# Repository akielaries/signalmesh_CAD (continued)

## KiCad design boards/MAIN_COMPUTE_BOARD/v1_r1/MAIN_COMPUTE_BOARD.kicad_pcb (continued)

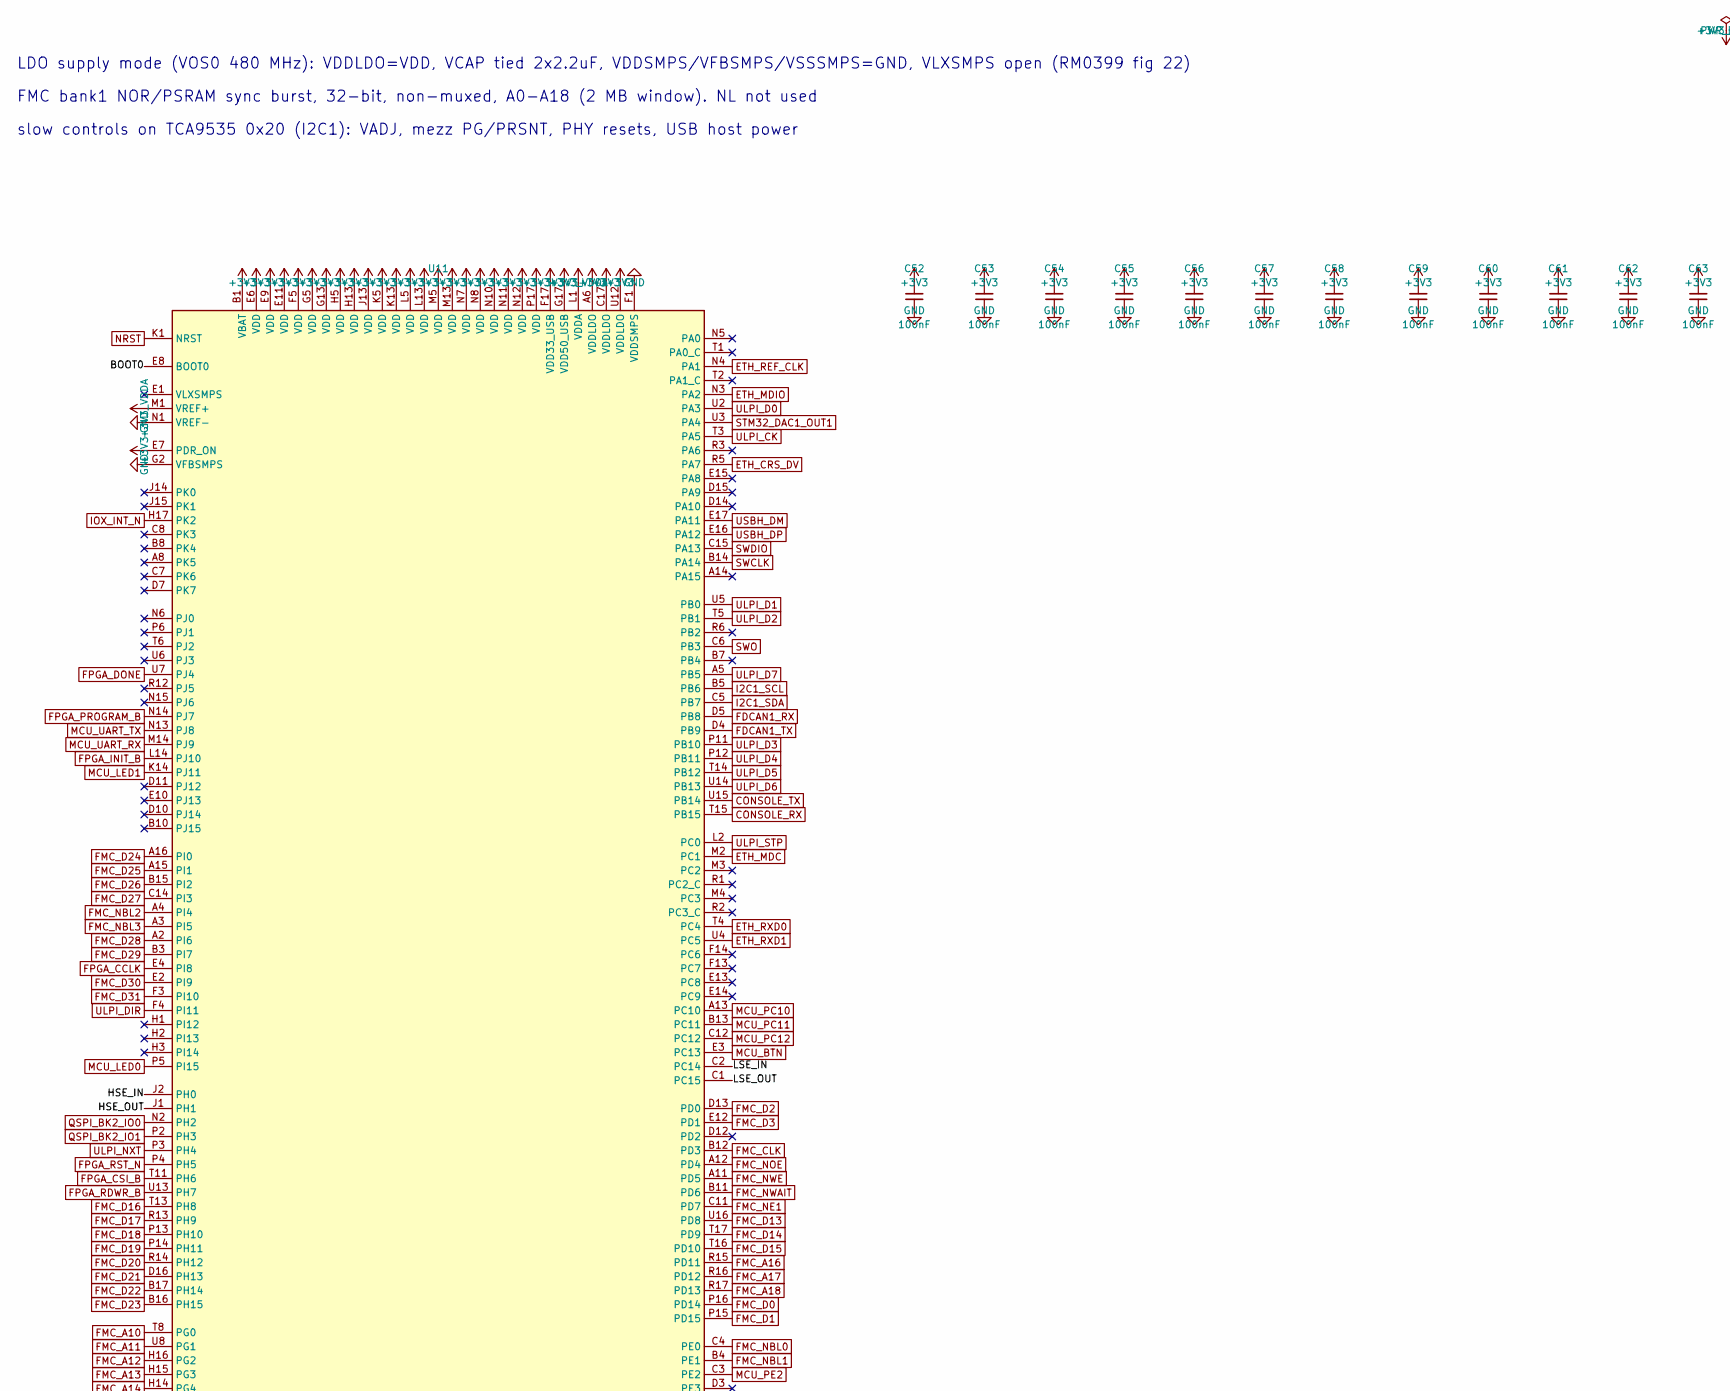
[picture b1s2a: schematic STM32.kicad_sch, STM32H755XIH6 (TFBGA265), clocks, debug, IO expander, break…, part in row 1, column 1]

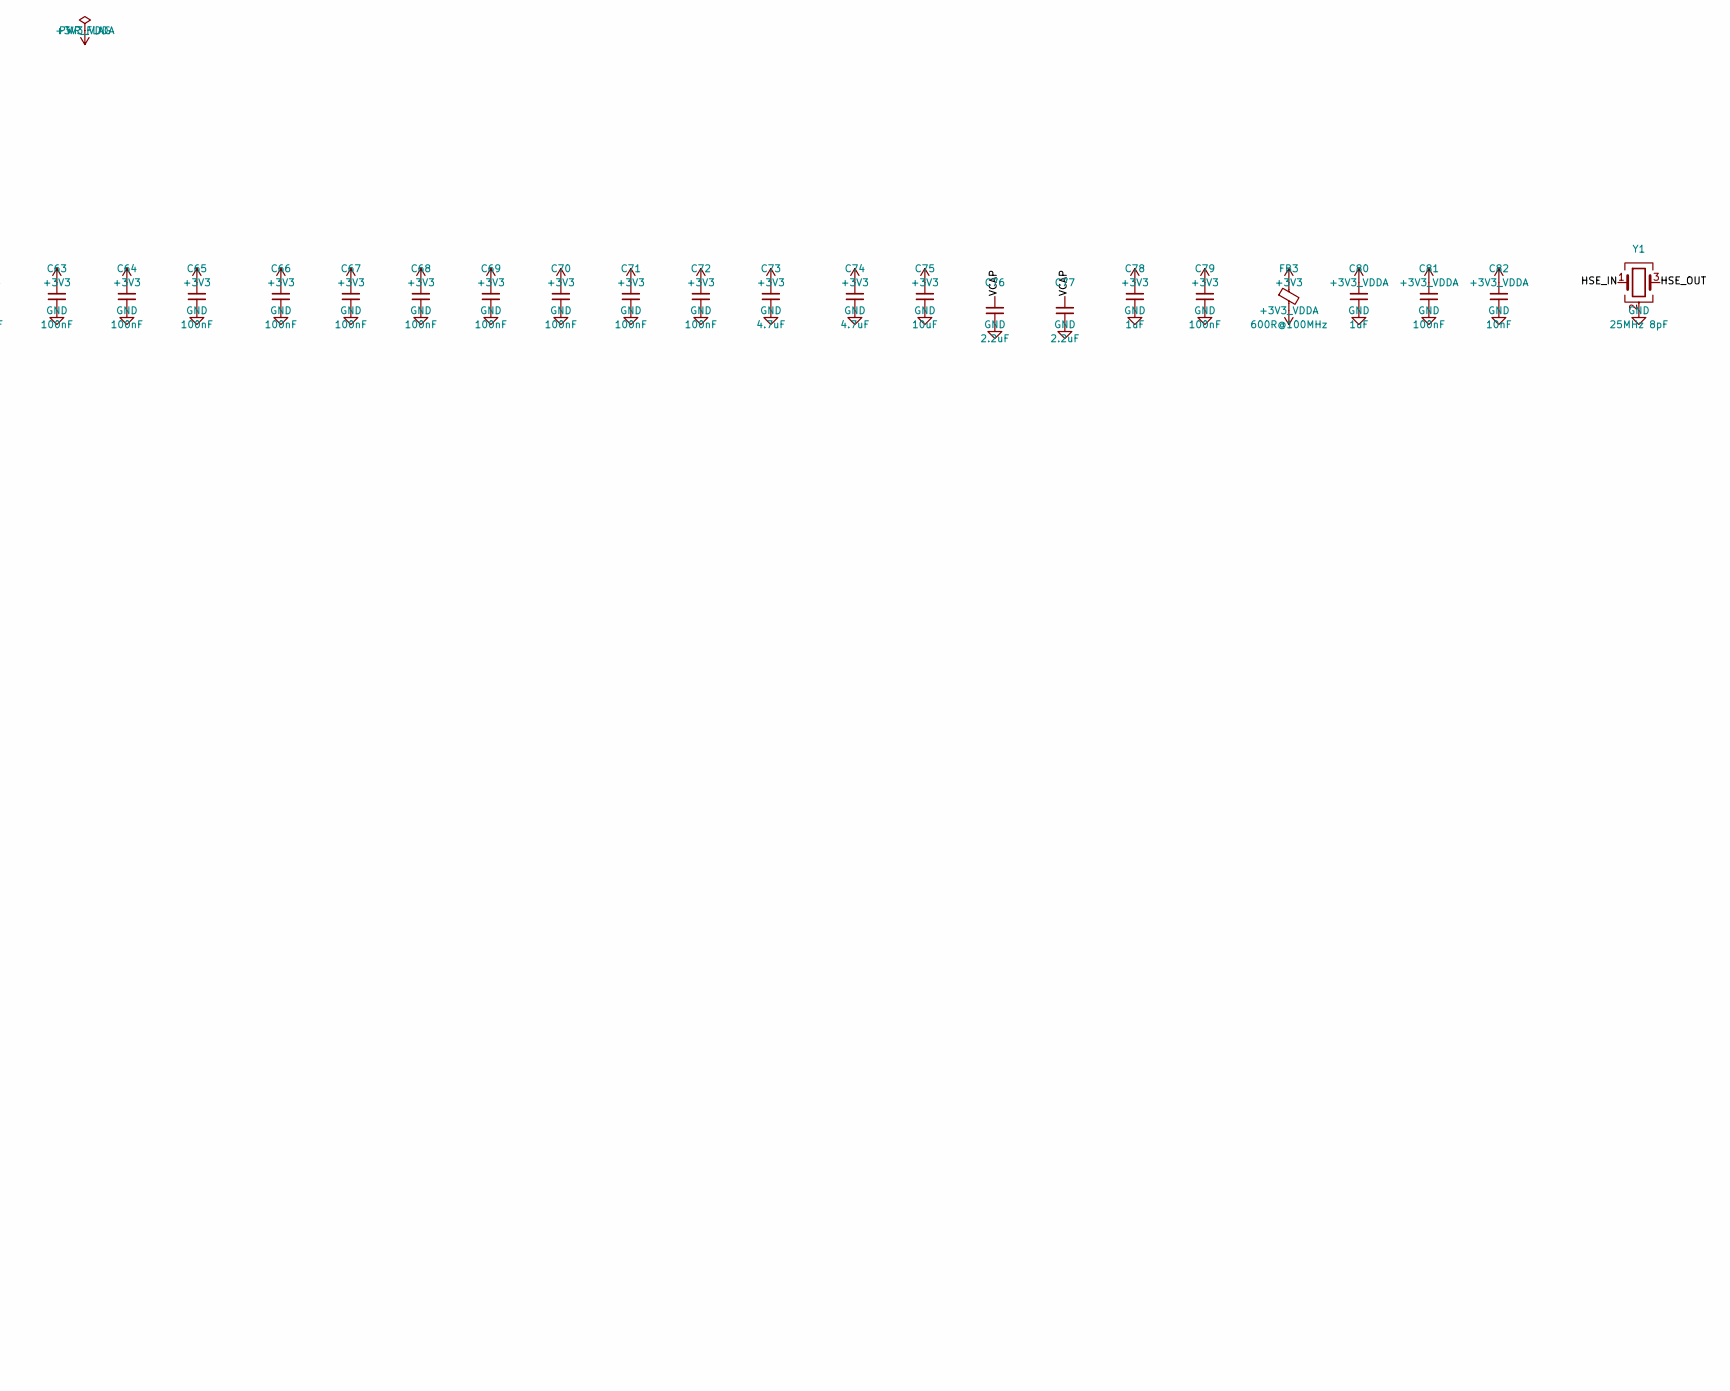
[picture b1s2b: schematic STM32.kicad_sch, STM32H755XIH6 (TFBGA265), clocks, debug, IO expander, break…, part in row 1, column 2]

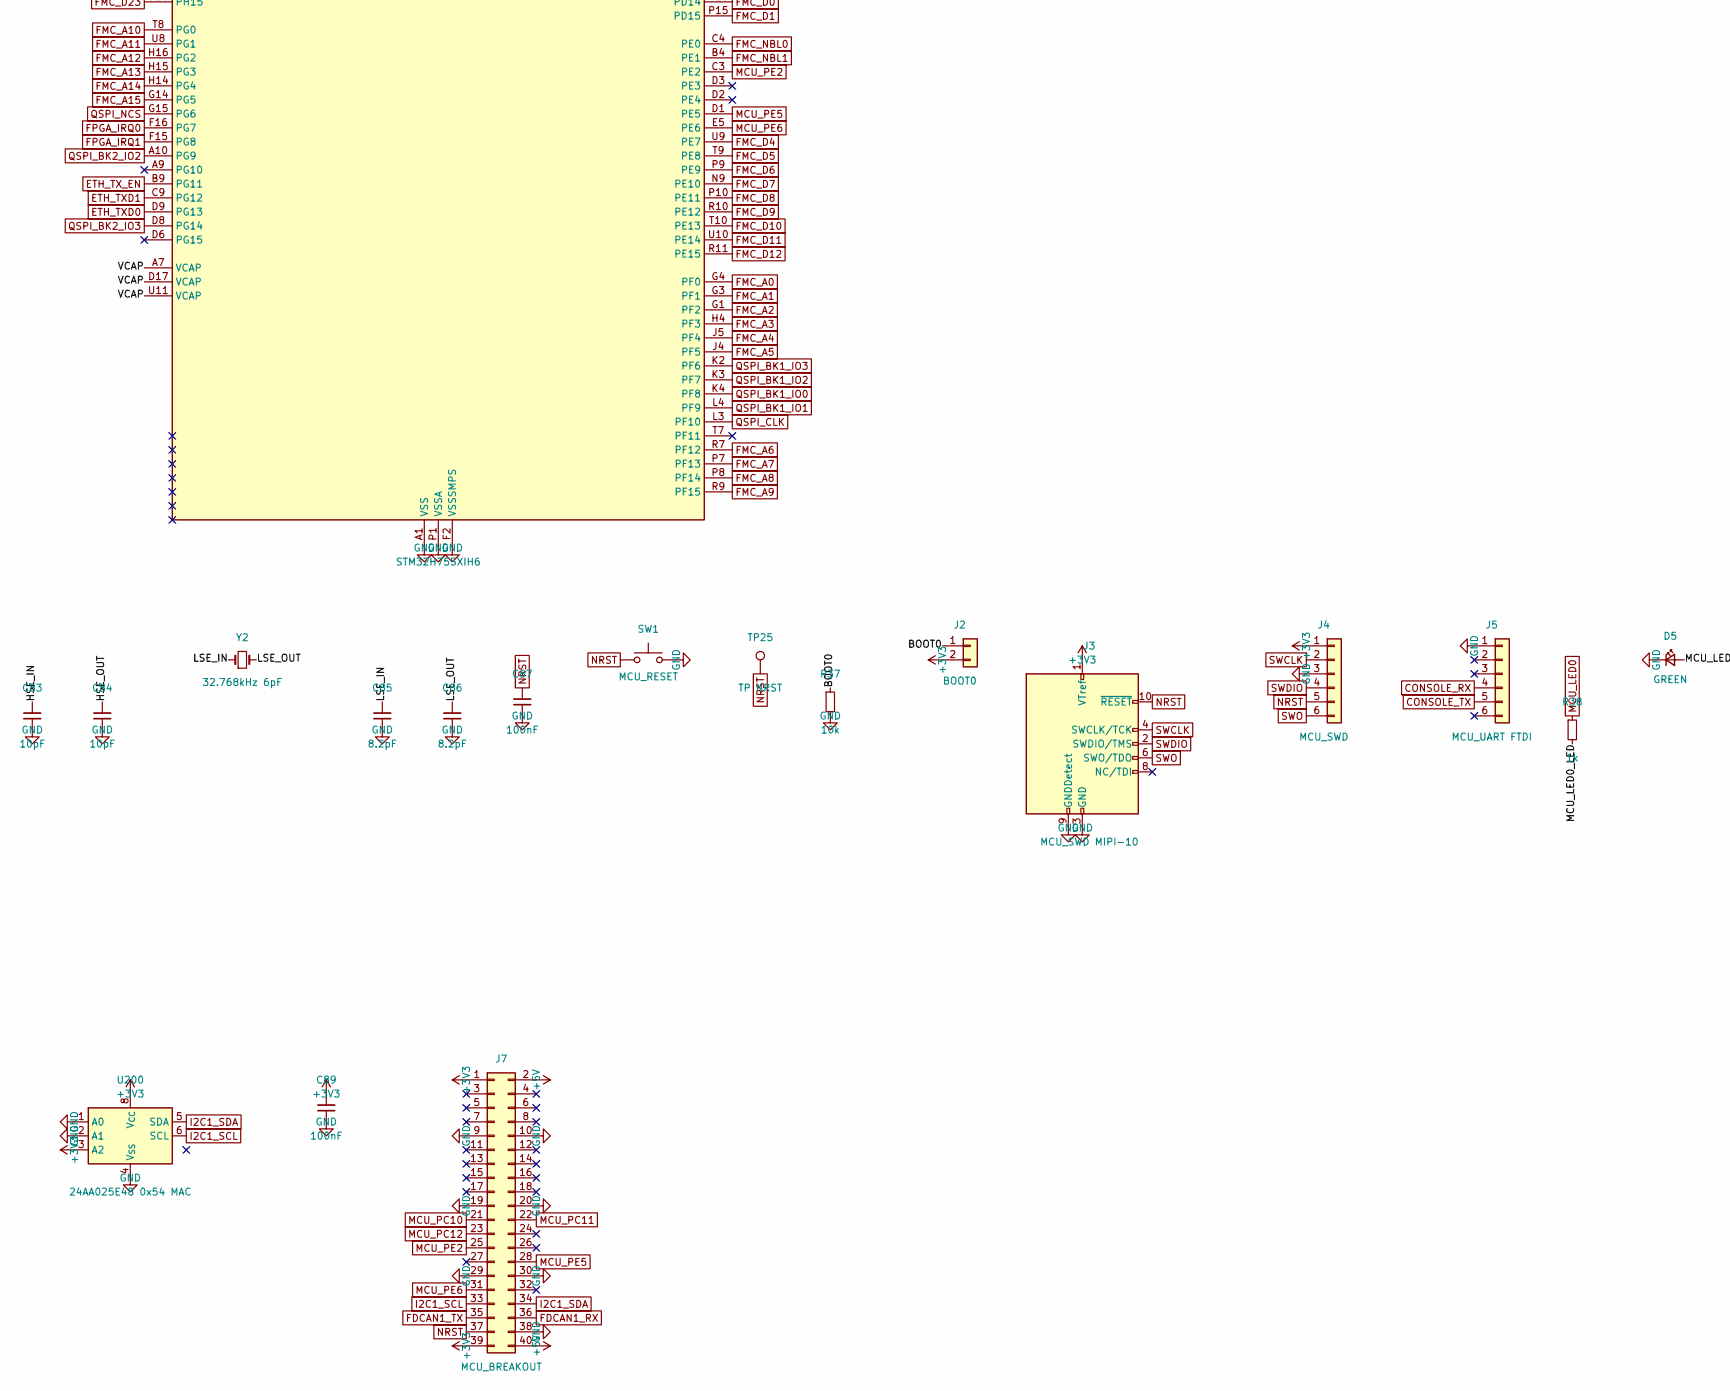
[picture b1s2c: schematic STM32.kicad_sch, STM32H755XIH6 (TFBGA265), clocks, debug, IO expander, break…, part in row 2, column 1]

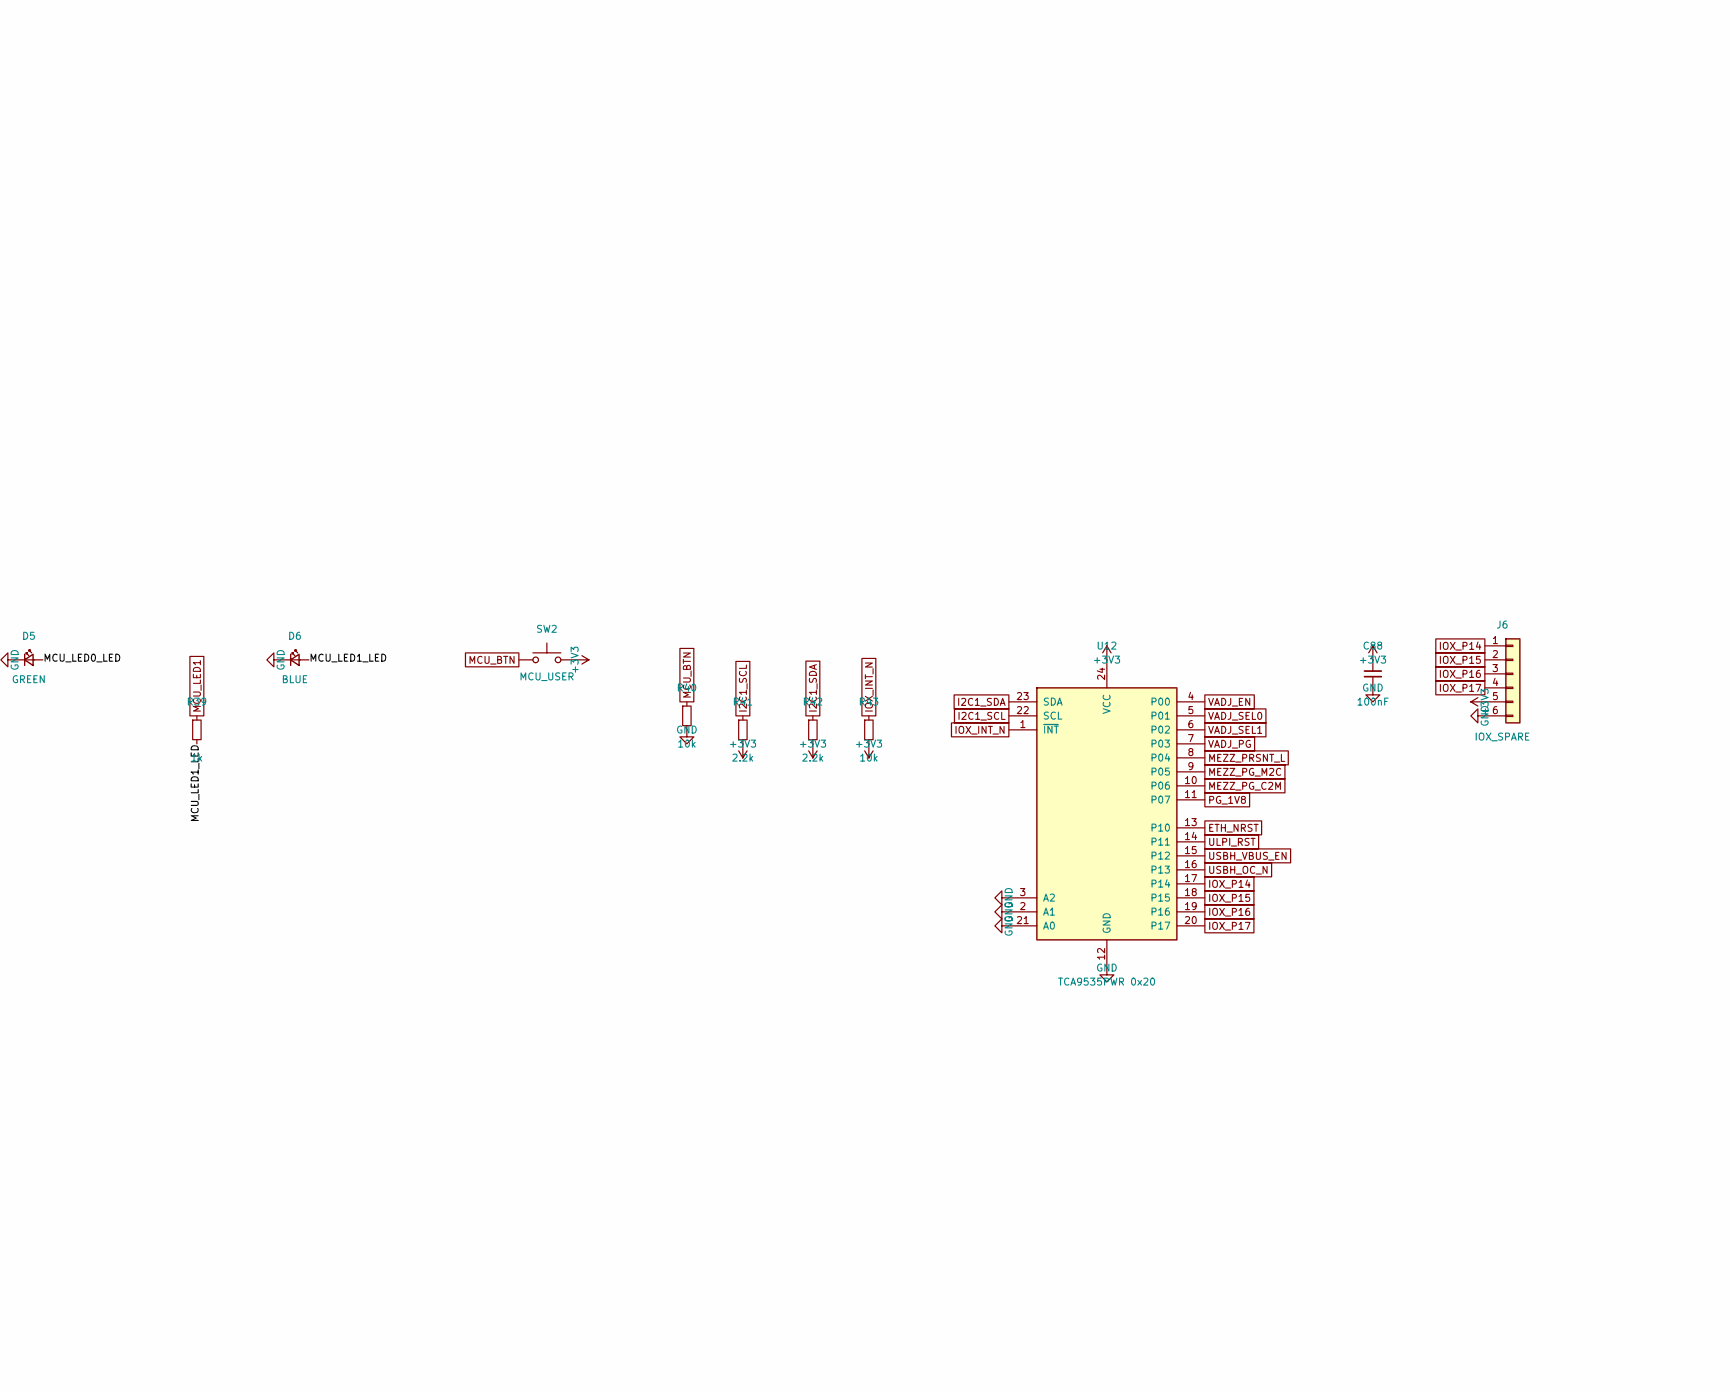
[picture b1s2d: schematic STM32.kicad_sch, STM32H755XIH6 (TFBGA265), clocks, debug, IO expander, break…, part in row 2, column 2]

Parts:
C52, C53, C54, C55, C56, C57, C58, C59, C60, C61, C62, C63, C64, C65, C66, C67, C68, C69, C70, C71, C72, C79, C81, C87, C88, C89: 100nF; C_0402_1005Metric
C73, C74: 4.7uF; C_0603_1608Metric
C75: 10uF; C_0805_2012Metric
C76, C77: 2.2uF; C_0603_1608Metric
C78, C80: 1uF; C_0402_1005Metric
C82: 10nF; C_0402_1005Metric
C83, C84: 10pF; C_0402_1005Metric
C85, C86: 8.2pF; C_0402_1005Metric
D5: GREEN; LED_0603_1608Metric
D6: BLUE; LED_0603_1608Metric
FB3: 600R@100MHz; L_0603_1608Metric
J2: BOOT0; PinHeader_1x02_P2.54mm_Vertical
J3: MCU_SWD MIPI-10; PinHeader_2x05_P1.27mm_Vertical_SMD
J4: MCU_SWD; PinHeader_1x06_P2.54mm_Vertical
J5: MCU_UART FTDI; PinHeader_1x06_P2.54mm_Vertical
J6: IOX_SPARE; PinHeader_1x06_P2.54mm_Vertical
J7: MCU_BREAKOUT; PinHeader_2x20_P2.54mm_Vertical
R37, R40, R43: 10k; R_0402_1005Metric
R38, R39: 1k; R_0402_1005Metric
R41, R42: 2.2k; R_0402_1005Metric
SW1: MCU_RESET; SW_SPST_TL3342
SW2: MCU_USER; SW_SPST_TL3342
TP25: TP NRST; TestPoint_Pad_D1.5mm
U11: STM32H755XIH6; TFBGA-265_14x14mm_Layout17x17_P0.8mm
U12: TCA9535PWR 0x20; TSSOP-24_4.4x7.8mm_P0.65mm
U200: 24AA025E48 0x54 MAC; SOIC-8_3.9x4.9mm_P1.27mm
Y1: 25MHz 8pF; Crystal_SMD_3225-4Pin_3.2x2.5mm
Y2: 32.768kHz 6pF; Crystal_SMD_3215-2Pin_3.2x1.5mm

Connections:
+3V3: C52.1, C53.1, C54.1, C55.1, C56.1, C57.1, C58.1, C59.1, C60.1, C61.1, C62.1, C63.1, C64.1, C65.1, C66.1, C67.1, C68.1, C69.1, C70.1, C71.1, C72.1, C73.1, C74.1, C75.1, C78.1, C79.1, C88.1, C89.1, FB3.1, J2.2, J3.1 (VTref), J4.1, J6.5, J7.1, J7.39, R41.2, R42.2, R43.2, SW2.2, U11.A6 (VDDLDO), U11.B1 (VBAT), U11.C17 (VDDLDO), U11.E6 (VDD), U11.E7 (PDR_ON), U11.E9 (VDD), U11.E11 (VDD), U11.F5 (VDD), U11.F17 (VDD33_USB), U11.G5 (VDD), U11.G13 (VDD), U11.G17 (VDD50_USB), U11.H5 (VDD), U11.H13 (VDD), U11.J13 (VDD), U11.K5 (VDD), U11.K13 (VDD), U11.L5 (VDD), U11.L13 (VDD), U11.M5 (VDD), U11.M13 (VDD), U11.N7 (VDD), U11.N8 (VDD), U11.N10 (VDD), U11.N11 (VDD), U11.N12 (VDD), U11.P17 (VDD), U11.U12 (VDDLDO), U12.24 (VCC), U200.3 (A2), U200.8 (V_{CC}); also elsewhere on the board
+3V3_VDDA: C80.1, C81.1, C82.1, FB3.2, U11.L1 (VDDA), U11.M1 (VREF+)
+5V: J7.2, J7.40; also elsewhere on the board
/STM32/BOOT0: J2.1, R37.1, U11.E8 (BOOT0)
/STM32/HSE_IN: C83.1, U11.J2 (PH0), Y1.1
/STM32/HSE_OUT: C84.1, U11.J1 (PH1), Y1.3
/STM32/LSE_IN: C85.1, U11.C2 (PC14), Y2.1
/STM32/LSE_OUT: C86.1, U11.C1 (PC15), Y2.2
/STM32/MCU_LED0_LED: D5.2 (A), R38.2
/STM32/MCU_LED1_LED: D6.2 (A), R39.2
/STM32/VCAP: C76.1, C77.1, U11.A7 (VCAP), U11.D17 (VCAP), U11.U11 (VCAP)
CONSOLE_RX: J5.4, U11.T15 (PB15)
CONSOLE_TX: J5.5, U11.U15 (PB14)
ETH_CRS_DV: U11.R5 (PA7); also elsewhere on the board
ETH_MDC: U11.M2 (PC1); also elsewhere on the board
ETH_MDIO: U11.N3 (PA2); also elsewhere on the board
ETH_NRST: U12.13 (P10); also elsewhere on the board
ETH_REF_CLK: U11.N4 (PA1); also elsewhere on the board
ETH_RXD0: U11.T4 (PC4); also elsewhere on the board
ETH_RXD1: U11.U4 (PC5); also elsewhere on the board
ETH_TXD0: U11.D9 (PG13); also elsewhere on the board
ETH_TXD1: U11.C9 (PG12); also elsewhere on the board
ETH_TX_EN: U11.B9 (PG11); also elsewhere on the board
FDCAN1_RX: J7.36, U11.D5 (PB8); also elsewhere on the board
FDCAN1_TX: J7.35, U11.D4 (PB9); also elsewhere on the board
FMC_A0: U11.G4 (PF0); also elsewhere on the board
FMC_A1: U11.G3 (PF1); also elsewhere on the board
FMC_A2: U11.G1 (PF2); also elsewhere on the board
FMC_A3: U11.H4 (PF3); also elsewhere on the board
FMC_A4: U11.J5 (PF4); also elsewhere on the board
FMC_A5: U11.J4 (PF5); also elsewhere on the board
FMC_A6: U11.R7 (PF12); also elsewhere on the board
FMC_A7: U11.P7 (PF13); also elsewhere on the board
FMC_A8: U11.P8 (PF14); also elsewhere on the board
FMC_A9: U11.R9 (PF15); also elsewhere on the board
FMC_A10: U11.T8 (PG0); also elsewhere on the board
FMC_A11: U11.U8 (PG1); also elsewhere on the board
FMC_A12: U11.H16 (PG2); also elsewhere on the board
FMC_A13: U11.H15 (PG3); also elsewhere on the board
FMC_A14: U11.H14 (PG4); also elsewhere on the board
FMC_A15: U11.G14 (PG5); also elsewhere on the board
FMC_A16: U11.R15 (PD11); also elsewhere on the board
FMC_A17: U11.R16 (PD12); also elsewhere on the board
FMC_A18: U11.R17 (PD13); also elsewhere on the board
FMC_CLK: U11.B12 (PD3); also elsewhere on the board
FMC_D0: U11.P16 (PD14); also elsewhere on the board
FMC_D1: U11.P15 (PD15); also elsewhere on the board
FMC_D2: U11.D13 (PD0); also elsewhere on the board
FMC_D3: U11.E12 (PD1); also elsewhere on the board
FMC_D4: U11.U9 (PE7); also elsewhere on the board
FMC_D5: U11.T9 (PE8); also elsewhere on the board
FMC_D6: U11.P9 (PE9); also elsewhere on the board
FMC_D7: U11.N9 (PE10); also elsewhere on the board
FMC_D8: U11.P10 (PE11); also elsewhere on the board
FMC_D9: U11.R10 (PE12); also elsewhere on the board
FMC_D10: U11.T10 (PE13); also elsewhere on the board
FMC_D11: U11.U10 (PE14); also elsewhere on the board
FMC_D12: U11.R11 (PE15); also elsewhere on the board
FMC_D13: U11.U16 (PD8); also elsewhere on the board
FMC_D14: U11.T17 (PD9); also elsewhere on the board
FMC_D15: U11.T16 (PD10); also elsewhere on the board
FMC_D16: U11.T13 (PH8); also elsewhere on the board
FMC_D17: U11.R13 (PH9); also elsewhere on the board
FMC_D18: U11.P13 (PH10); also elsewhere on the board
FMC_D19: U11.P14 (PH11); also elsewhere on the board
FMC_D20: U11.R14 (PH12); also elsewhere on the board
FMC_D21: U11.D16 (PH13); also elsewhere on the board
FMC_D22: U11.B17 (PH14); also elsewhere on the board
FMC_D23: U11.B16 (PH15); also elsewhere on the board
FMC_D24: U11.A16 (PI0); also elsewhere on the board
FMC_D25: U11.A15 (PI1); also elsewhere on the board
FMC_D26: U11.B15 (PI2); also elsewhere on the board
FMC_D27: U11.C14 (PI3); also elsewhere on the board
FMC_D28: U11.A2 (PI6); also elsewhere on the board
FMC_D29: U11.B3 (PI7); also elsewhere on the board
FMC_D30: U11.E2 (PI9); also elsewhere on the board
FMC_D31: U11.F3 (PI10); also elsewhere on the board
FMC_NBL0: U11.C4 (PE0); also elsewhere on the board
FMC_NBL1: U11.B4 (PE1); also elsewhere on the board
FMC_NBL2: U11.A4 (PI4); also elsewhere on the board
FMC_NBL3: U11.A3 (PI5); also elsewhere on the board
FMC_NE1: U11.C11 (PD7); also elsewhere on the board
FMC_NOE: U11.A12 (PD4); also elsewhere on the board
FMC_NWAIT: U11.B11 (PD6); also elsewhere on the board
FMC_NWE: U11.A11 (PD5); also elsewhere on the board
FPGA_CCLK: U11.E4 (PI8); also elsewhere on the board
FPGA_CSI_B: U11.T11 (PH6); also elsewhere on the board
FPGA_DONE: U11.U7 (PJ4); also elsewhere on the board
FPGA_INIT_B: U11.L14 (PJ10); also elsewhere on the board
FPGA_IRQ0: U11.F16 (PG7); also elsewhere on the board
FPGA_IRQ1: U11.F15 (PG8); also elsewhere on the board
FPGA_PROGRAM_B: U11.N14 (PJ7); also elsewhere on the board
FPGA_RDWR_B: U11.U13 (PH7); also elsewhere on the board
FPGA_RST_N: U11.P4 (PH5); also elsewhere on the board
GND: C52.2, C53.2, C54.2, C55.2, C56.2, C57.2, C58.2, C59.2, C60.2, C61.2, C62.2, C63.2, C64.2, C65.2, C66.2, C67.2, C68.2, C69.2, C70.2, C71.2, C72.2, C73.2, C74.2, C75.2, C76.2, C77.2, C78.2, C79.2, C80.2, C81.2, C82.2, C83.2, C84.2, C85.2, C86.2, C87.2, C88.2, C89.2, D5.1 (K), D6.1 (K), J3.3 (GND), J3.5 (GND), J3.9 (GNDDetect), J4.3, J5.1, J6.6, J7.9, J7.10, J7.19, J7.20, J7.29, J7.30, J7.38, R37.2, R40.2, SW1.2, U11.A1 (VSS), U11.A17 (VSS), U11.B2 (VSS), U11.B6 (VSS), U11.C10 (VSS), U11.C13 (VSS), U11.C16 (VSS), U11.F1 (VDDSMPS), U11.F2 (VSSSMPS), U11.G2 (VFBSMPS), U11.G7 (VSS), U11.G8 (VSS), U11.G9 (VSS), U11.G10 (VSS), U11.G11 (VSS), U11.G16 (VSS), U11.H7 (VSS), U11.H8 (VSS), U11.H9 (VSS), U11.H10 (VSS), U11.H11 (VSS), U11.J3 (VSS), U11.J7 (VSS), U11.J8 (VSS), U11.J9 (VSS), U11.J10 (VSS), U11.J11 (VSS), U11.J16 (VSS), U11.J17 (VSS), U11.K7 (VSS), U11.K8 (VSS), U11.K9 (VSS), U11.K10 (VSS), U11.K11 (VSS), U11.K15 (VSS), U11.L7 (VSS), U11.L8 (VSS), U11.L9 (VSS), U11.L10 (VSS), U11.L11 (VSS), U11.L15 (VSS), U11.M15 (VSS), U11.N1 (VREF-), U11.N16 (VSS), U11.P1 (VSSA), U11.R4 (VSS), U11.R8 (VSS), U11.T12 (VSS), U11.U1 (VSS), U11.U17 (VSS), U12.2 (A1), U12.3 (A2), U12.12 (GND), U12.21 (A0), U200.1 (A0), U200.2 (A1), U200.4 (V_{SS}), Y1.2 (G), Y1.4 (G); also elsewhere on the board
I2C1_SCL: J7.33, R41.1, U11.B5 (PB6), U12.22 (SCL), U200.6 (SCL); also elsewhere on the board
I2C1_SDA: J7.34, R42.1, U11.C5 (PB7), U12.23 (SDA), U200.5 (SDA); also elsewhere on the board
IOX_INT_N: R43.1, U11.H17 (PK2), U12.1 (~INT)
IOX_P14: J6.1, U12.17 (P14)
IOX_P15: J6.2, U12.18 (P15)
IOX_P16: J6.3, U12.19 (P16)
IOX_P17: J6.4, U12.20 (P17)
MCU_BTN: R40.1, SW2.1, U11.E3 (PC13)
MCU_LED0: R38.1, U11.P5 (PI15)
MCU_LED1: R39.1, U11.K14 (PJ11)
MCU_PC10: J7.21, U11.A13 (PC10)
MCU_PC11: J7.22, U11.B13 (PC11)
MCU_PC12: J7.23, U11.C12
MCU_PE2: J7.25, U11.C3 (PE2)
MCU_PE5: J7.28, U11.D1 (PE5)
MCU_PE6: J7.31, U11.E5 (PE6)
MCU_UART_RX: U11.M14 (PJ9); also elsewhere on the board
MCU_UART_TX: U11.N13 (PJ8); also elsewhere on the board
MEZZ_PG_C2M: U12.10 (P06); also elsewhere on the board
MEZZ_PG_M2C: U12.9 (P05); also elsewhere on the board
MEZZ_PRSNT_L: U12.8 (P04); also elsewhere on the board
NRST: C87.1, J3.10 (~RESET), J4.5, J7.37, SW1.1, TP25.1, U11.K1 (NRST)
PG_1V8: U12.11 (P07); also elsewhere on the board
QSPI_BK1_IO0: U11.K4 (PF8); also elsewhere on the board
QSPI_BK1_IO1: U11.L4 (PF9); also elsewhere on the board
QSPI_BK1_IO2: U11.K3 (PF7); also elsewhere on the board
QSPI_BK1_IO3: U11.K2 (PF6); also elsewhere on the board
QSPI_BK2_IO0: U11.N2 (PH2); also elsewhere on the board
QSPI_BK2_IO1: U11.P2 (PH3); also elsewhere on the board
QSPI_BK2_IO2: U11.A10 (PG9); also elsewhere on the board
QSPI_BK2_IO3: U11.D8 (PG14); also elsewhere on the board
QSPI_CLK: U11.L3 (PF10); also elsewhere on the board
QSPI_NCS: U11.G15 (PG6); also elsewhere on the board
STM32_DAC1_OUT1: U11.U3 (PA4); also elsewhere on the board
SWCLK: J3.4 (SWCLK/TCK), J4.2, U11.B14 (PA14)
SWDIO: J3.2 (SWDIO/TMS), J4.4, U11.C15 (PA13)
SWO: J3.6 (SWO/TDO), J4.6, U11.C6 (PB3)
ULPI_CK: U11.T3 (PA5); also elsewhere on the board
ULPI_D0: U11.U2 (PA3); also elsewhere on the board
ULPI_D1: U11.U5 (PB0); also elsewhere on the board
ULPI_D2: U11.T5 (PB1); also elsewhere on the board
ULPI_D3: U11.P11 (PB10); also elsewhere on the board
ULPI_D4: U11.P12 (PB11); also elsewhere on the board
ULPI_D5: U11.T14 (PB12); also elsewhere on the board
ULPI_D6: U11.U14 (PB13); also elsewhere on the board
ULPI_D7: U11.A5 (PB5); also elsewhere on the board
ULPI_DIR: U11.F4 (PI11); also elsewhere on the board
ULPI_NXT: U11.P3 (PH4); also elsewhere on the board
ULPI_RST: U12.14 (P11); also elsewhere on the board
ULPI_STP: U11.L2 (PC0); also elsewhere on the board
USBH_DM: U11.E17 (PA11); also elsewhere on the board
USBH_DP: U11.E16 (PA12); also elsewhere on the board
USBH_OC_N: U12.16 (P13); also elsewhere on the board
USBH_VBUS_EN: U12.15 (P12); also elsewhere on the board
VADJ_EN: U12.4 (P00); also elsewhere on the board
VADJ_PG: U12.7 (P03); also elsewhere on the board
VADJ_SEL0: U12.5 (P01); also elsewhere on the board
VADJ_SEL1: U12.6 (P02); also elsewhere on the board

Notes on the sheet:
LDO supply mode (VOS0 480 MHz): VDDLDO=VDD, VCAP tied 2x2.2uF, VDDSMPS/VFBSMPS/VSSSMPS=GND, VLXSMPS open (RM0399 fig 22)
FMC bank1 NOR/PSRAM sync burst, 32-bit, non-muxed, A0-A18 (2 MB window). NL not used
slow controls on TCA9535 0x20 (I2C1): VADJ, mezz PG/PRSNT, PHY resets, USB host power
